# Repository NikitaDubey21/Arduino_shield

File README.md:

# Arduino_shield
**Description**: Designed a 4-digit 7 segment Arduino shield PCB layout using Autodesk Eagle, aimed at extending the functionality of Arduino microcontrollers for specific applications.

**Key Contributions:**

Developed schematic and board layout designs for the Arduino shield to ensure compatibility and functionality with Arduino microcontrollers.

Utilized Autodesk Eagle software to create and optimize the PCB layout, considering factors such as component placement and routing constraints.

**Technologies Used**:

Autodesk Eagle PCB design software

Circuit design and layout principles

**Skills Demonstrated**:

Proficiency in PCB design using Autodesk Eagle, including schematic capture, component placement, and routing.

Understanding of electronics and circuit design principles to ensure functional and reliable PCB layouts.

**Outcome**: Successfully designed and implemented a 4-digit 7 segment Arduino shield PCB layout, demonstrating expertise in PCB design and proficiency with Autodesk Eagle software.

**Schematic Image**

**Board Layout**

**Manufacturing Preview**

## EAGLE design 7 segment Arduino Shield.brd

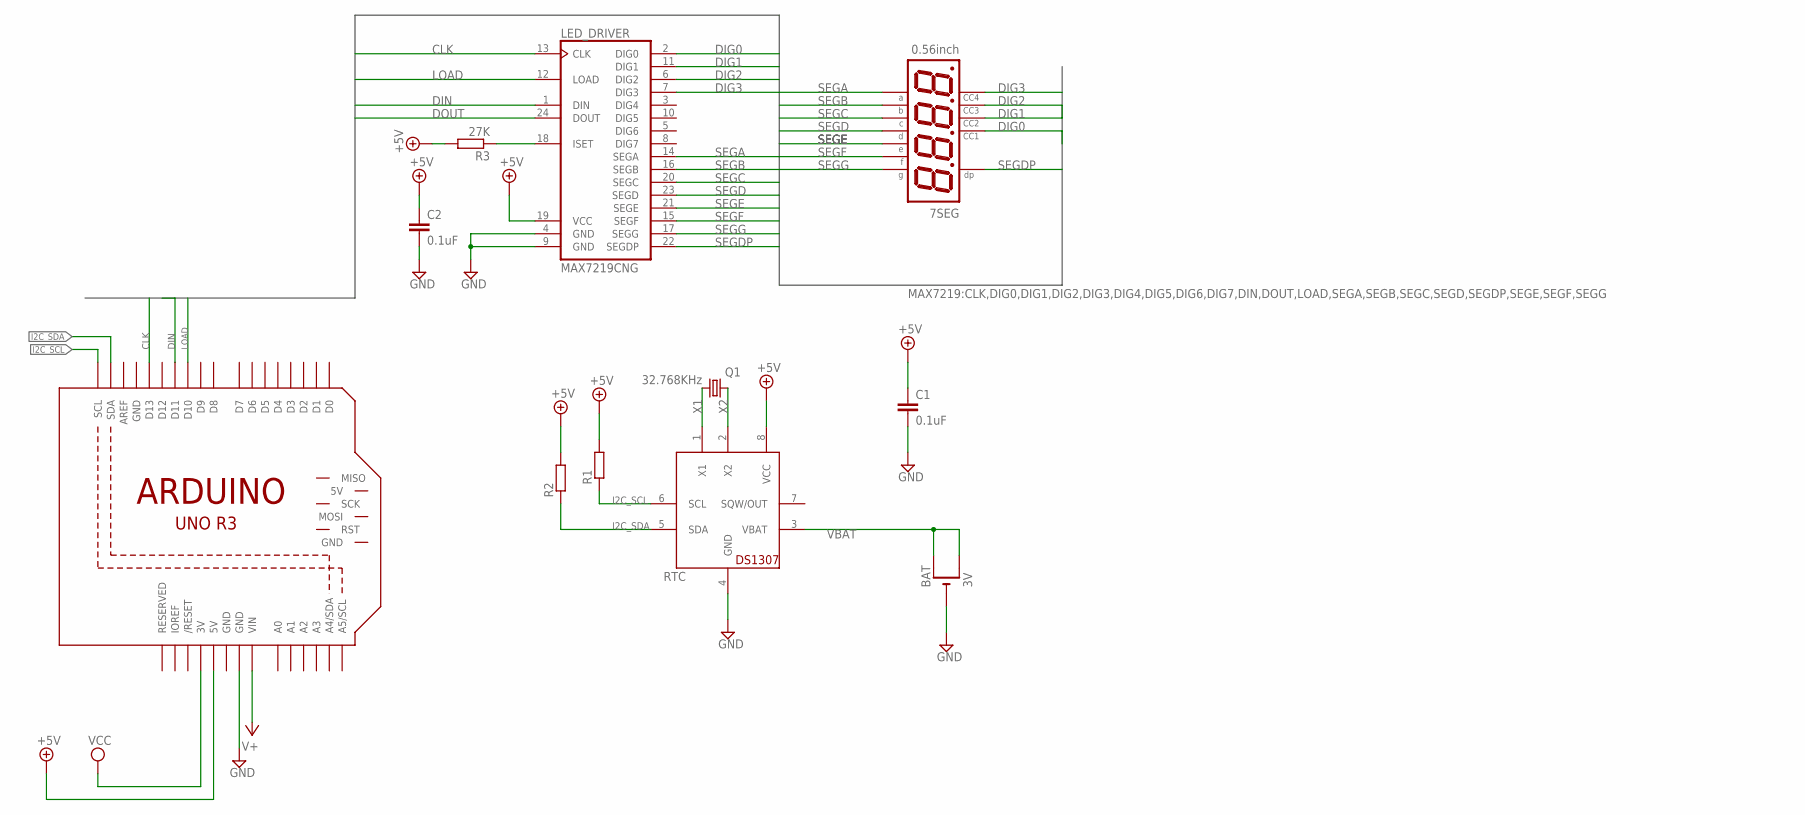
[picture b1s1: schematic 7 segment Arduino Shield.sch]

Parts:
7SEG: 0.56inch; NFD-5641
BAT: 3V; CR1220-SMD
C1: 0.1uF; C050-030X075
C2: 0.1uF; C1206
LED_DRIVER: MAX7219CNG; DIL24-3
M1: ARDUINO_R3_ICSP; ARDUINOR3_ICSP
Q1: 32.768KHz; TC26H
R1, R2: R-EU_M1206; M1206
R3: 27K; M1206
RTC: DS1307; DIL08

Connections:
+5V: C1.1, C2.1, LED_DRIVER.19 (VCC), M1.5V, R1.2, R2.2, R3.2, RTC.8 (VCC)
CLK: LED_DRIVER.13 (CLK), M1.D13
DIG0: 7SEG.P$12, LED_DRIVER.2 (DIG0)
DIG1: 7SEG.P$9, LED_DRIVER.11 (DIG1)
DIG2: 7SEG.P$8, LED_DRIVER.6 (DIG2)
DIG3: 7SEG.P$6, LED_DRIVER.7 (DIG3)
DIN: LED_DRIVER.1 (DIN), M1.D11
DOUT: LED_DRIVER.24 (DOUT)
GND: BAT.-, C1.2, C2.2, LED_DRIVER.4 (GND), LED_DRIVER.9 (GND), M1.GND, M1.GND@1 (GND), M1.GND@3 (GND), RTC.4 (GND)
I2C_SCL: M1.SCL, R1.1, RTC.6 (SCL)
I2C_SDA: M1.SDA, R2.1, RTC.5 (SDA)
LOAD: LED_DRIVER.12 (LOAD), M1.D10
unnamed: LED_DRIVER.18 (ISET), R3.1
SEGA: 7SEG.P$11, LED_DRIVER.14 (SEGA)
SEGB: 7SEG.P$7, LED_DRIVER.16 (SEGB)
SEGC: 7SEG.P$4, LED_DRIVER.20 (SEGC)
SEGD: 7SEG.P$2, LED_DRIVER.23 (SEGD)
SEGDP: 7SEG.P$3, LED_DRIVER.22 (SEGDP)
SEGE: 7SEG.P$1, LED_DRIVER.21 (SEGE)
SEGF: 7SEG.P$10, LED_DRIVER.15 (SEGF)
SEGG: 7SEG.P$5, LED_DRIVER.17 (SEGG)
V+: M1.VIN
VBAT: BAT.+$1 (+), BAT.+$2 (+1), RTC.3 (VBAT)
VCC: M1.3V
X1: Q1.2, RTC.1 (X1)
X2: Q1.1, RTC.2 (X2)

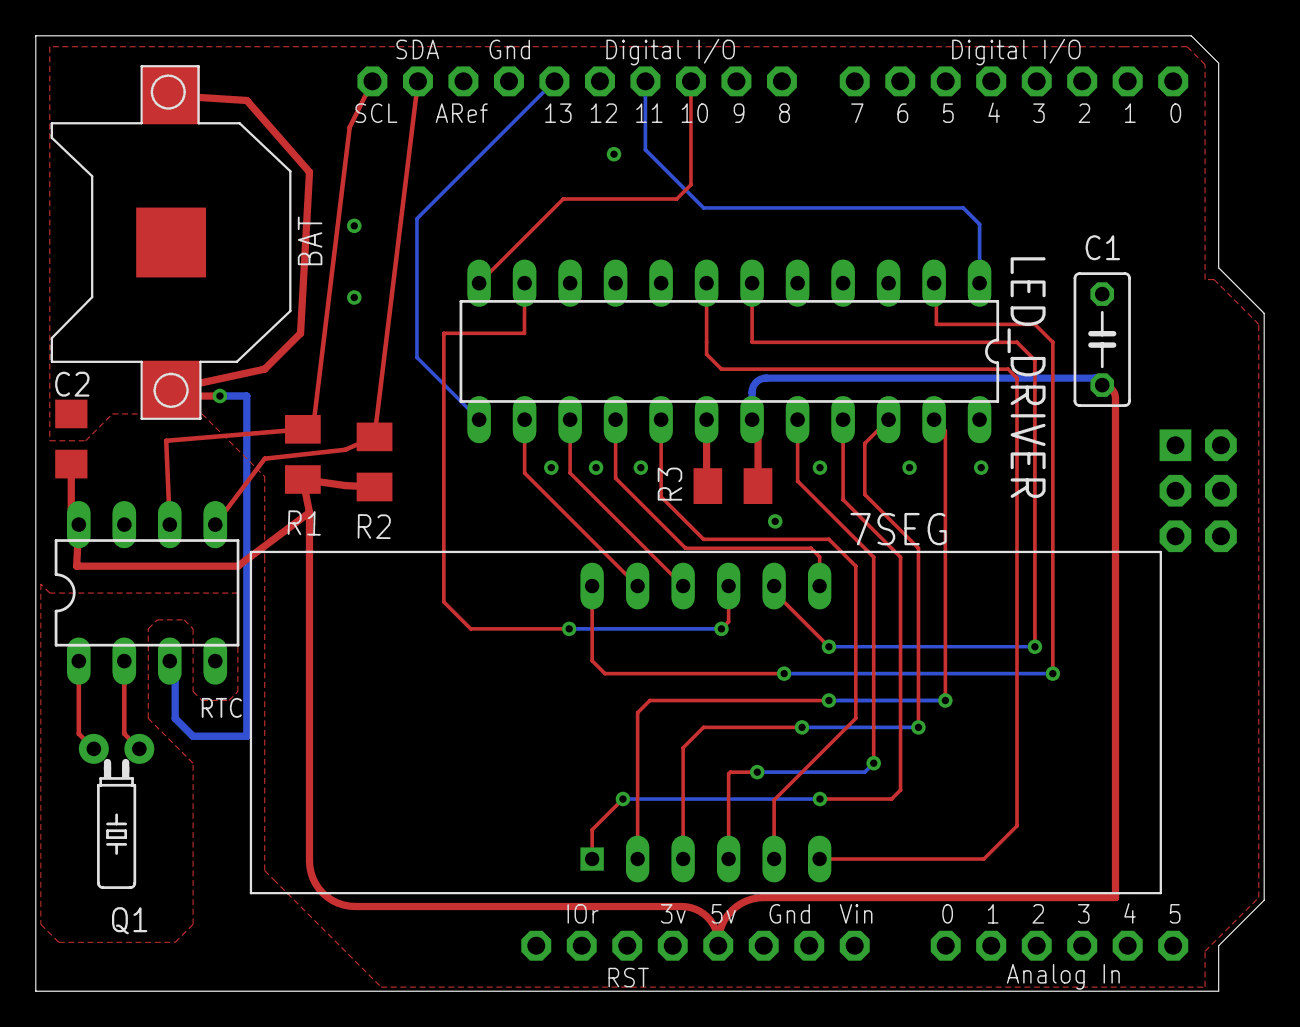
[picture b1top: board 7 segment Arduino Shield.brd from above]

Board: 2 copper layers, 68.6 x 53.3 mm, 11 parts (0 on the bottom side), 23 nets.
